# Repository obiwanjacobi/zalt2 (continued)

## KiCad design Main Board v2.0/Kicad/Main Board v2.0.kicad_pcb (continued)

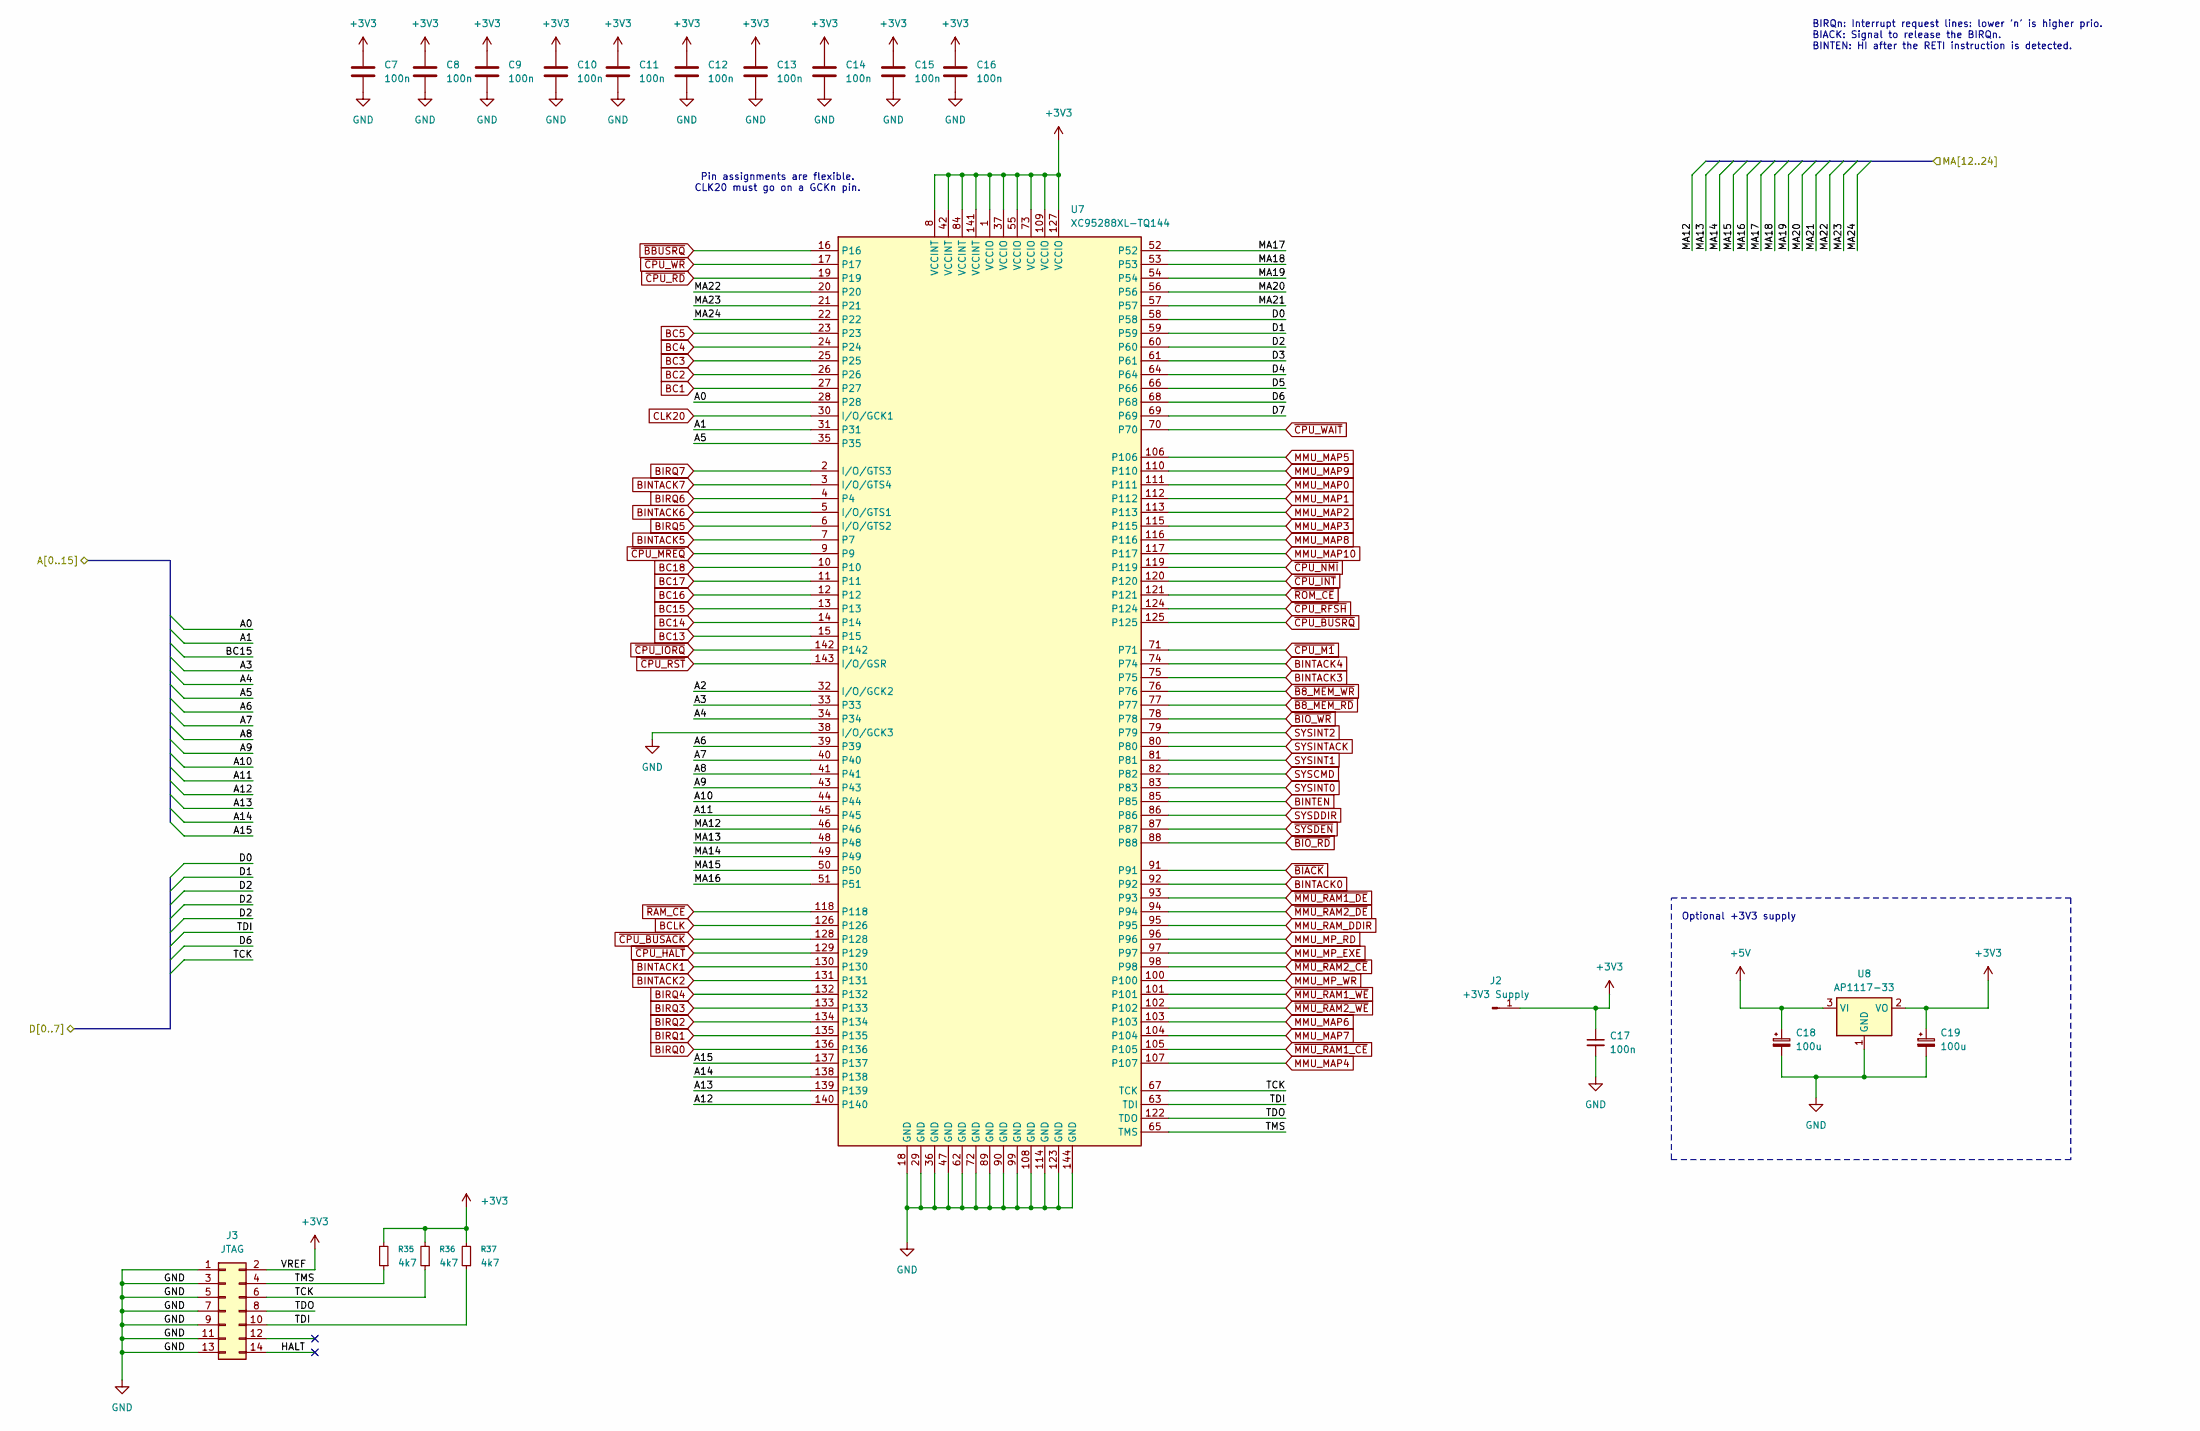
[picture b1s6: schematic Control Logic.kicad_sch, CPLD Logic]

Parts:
C7, C8, C9, C10, C11, C12, C13, C14, C15, C16, C17: 100n; C_0603_1608Metric_Pad1.08x0.95mm_HandSolder
C18, C19: 100u; CP_Radial_D8.0mm_P3.80mm
J2: +3V3 Supply; PinHeader_1x01_P2.54mm_Vertical
J3: JTAG; IDC-Header_2x07_P2.54mm_Vertical
R35, R36, R37: 4k7; R_0603_1608Metric_Pad0.98x0.95mm_HandSolder
U7: XC95288XL-TQ144; TQFP-144_20x20mm_P0.5mm
U8: AP1117-33; SOT-223-3_TabPin2

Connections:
+3V3: C7.1, C8.1, C9.1, C10.1, C11.1, C12.1, C13.1, C14.1, C15.1, C16.1, C17.1, C19.1, J2.1 (Pin_1_1), J3.2, R35.2, R36.2, R37.2, U7.1 (VCCIO), U7.8 (VCCINT), U7.37 (VCCIO), U7.42 (VCCINT), U7.55 (VCCIO), U7.73 (VCCIO), U7.84 (VCCINT), U7.109 (VCCIO), U7.127 (VCCIO), U7.141 (VCCINT), U8.2 (VO)
+5V: C18.1, U8.3 (VI); also elsewhere on the board
/CPU/A0: U7.28; also elsewhere on the board
/CPU/A1: U7.31; also elsewhere on the board
/CPU/A2: U7.32 (I/O/GCK2); also elsewhere on the board
/CPU/A3: U7.33; also elsewhere on the board
/CPU/A4: U7.34; also elsewhere on the board
/CPU/A5: U7.35; also elsewhere on the board
/CPU/A6: U7.39; also elsewhere on the board
/CPU/A7: U7.40; also elsewhere on the board
/CPU/A8: U7.41; also elsewhere on the board
/CPU/A9: U7.43; also elsewhere on the board
/CPU/A10: U7.44; also elsewhere on the board
/CPU/A11: U7.45; also elsewhere on the board
/CPU/A12: U7.140; also elsewhere on the board
/CPU/A13: U7.139; also elsewhere on the board
/CPU/A14: U7.138; also elsewhere on the board
/CPU/A15: U7.137; also elsewhere on the board
/CPU/D0: U7.58; also elsewhere on the board
/CPU/D1: U7.59; also elsewhere on the board
/CPU/D2: U7.60; also elsewhere on the board
/CPU/D3: U7.61; also elsewhere on the board
/CPU/D4: U7.64; also elsewhere on the board
/CPU/D5: U7.66; also elsewhere on the board
/CPU/D6: U7.68; also elsewhere on the board
/CPU/D7: U7.69; also elsewhere on the board
/Control Logic/HALT: J3.14
/Control Logic/MA12: U7.46; also elsewhere on the board
/Control Logic/MA13: U7.48; also elsewhere on the board
/Control Logic/MA14: U7.49; also elsewhere on the board
/Control Logic/MA15: U7.50; also elsewhere on the board
/Control Logic/MA16: U7.51; also elsewhere on the board
/Control Logic/MA17: U7.52; also elsewhere on the board
/Control Logic/MA18: U7.53; also elsewhere on the board
/Control Logic/MA19: U7.54; also elsewhere on the board
/Control Logic/MA20: U7.56; also elsewhere on the board
/Control Logic/MA21: U7.57; also elsewhere on the board
/Control Logic/MA22: U7.20; also elsewhere on the board
/Control Logic/MA23: U7.21; also elsewhere on the board
/Control Logic/MA24: U7.22; also elsewhere on the board
/Control Logic/TCK: J3.6, R36.1, U7.67 (TCK)
/Control Logic/TDI: J3.10, R37.1, U7.63 (TDI)
/Control Logic/TDO: J3.8, U7.122 (TDO)
/Control Logic/TMS: J3.4, R35.1, U7.65 (TMS)
BC1: U7.27; also elsewhere on the board
BC2: U7.26; also elsewhere on the board
BC3: U7.25; also elsewhere on the board
BC4: U7.24; also elsewhere on the board
BC5: U7.23; also elsewhere on the board
BC13: U7.15; also elsewhere on the board
BC14: U7.14; also elsewhere on the board
BC15: U7.13; also elsewhere on the board
BC16: U7.12; also elsewhere on the board
BC17: U7.11; also elsewhere on the board
BC18: U7.10; also elsewhere on the board
BCLK: U7.126; also elsewhere on the board
BINTACK0: U7.92; also elsewhere on the board
BINTACK1: U7.130; also elsewhere on the board
BINTACK2: U7.131; also elsewhere on the board
BINTACK3: U7.75; also elsewhere on the board
BINTACK4: U7.74; also elsewhere on the board
BINTACK5: U7.7; also elsewhere on the board
BINTACK6: U7.5 (I/O/GTS1); also elsewhere on the board
BINTACK7: U7.3 (I/O/GTS4); also elsewhere on the board
BINTEN: U7.85; also elsewhere on the board
BIRQ0: U7.136; also elsewhere on the board
BIRQ1: U7.135; also elsewhere on the board
BIRQ2: U7.134; also elsewhere on the board
BIRQ3: U7.133; also elsewhere on the board
BIRQ4: U7.132; also elsewhere on the board
BIRQ5: U7.6 (I/O/GTS2); also elsewhere on the board
BIRQ6: U7.4; also elsewhere on the board
BIRQ7: U7.2 (I/O/GTS3); also elsewhere on the board
CLK20: U7.30 (I/O/GCK1); also elsewhere on the board
GND: C7.2, C8.2, C9.2, C10.2, C11.2, C12.2, C13.2, C14.2, C15.2, C16.2, C17.2, C18.2, C19.2, J3.1, J3.3, J3.5, J3.7, J3.9, J3.11, J3.13, U7.18 (GND), U7.29 (GND), U7.36 (GND), U7.38 (I/O/GCK3), U7.47 (GND), U7.62 (GND), U7.72 (GND), U7.89 (GND), U7.90 (GND), U7.99 (GND), U7.108 (GND), U7.114 (GND), U7.123 (GND), U7.144 (GND), U8.1 (GND); also elsewhere on the board
MMU_MAP0: U7.111; also elsewhere on the board
MMU_MAP1: U7.112; also elsewhere on the board
MMU_MAP2: U7.113; also elsewhere on the board
MMU_MAP3: U7.115; also elsewhere on the board
MMU_MAP4: U7.107; also elsewhere on the board
MMU_MAP5: U7.106; also elsewhere on the board
MMU_MAP6: U7.103; also elsewhere on the board
MMU_MAP7: U7.104; also elsewhere on the board
MMU_MAP8: U7.116; also elsewhere on the board
MMU_MAP9: U7.110; also elsewhere on the board
MMU_MAP10: U7.117; also elsewhere on the board
MMU_MP_EXE: U7.97; also elsewhere on the board
MMU_MP_RD: U7.96; also elsewhere on the board
MMU_MP_WR: U7.100; also elsewhere on the board
MMU_RAM_DDIR: U7.95; also elsewhere on the board
SYSCMD: U7.82; also elsewhere on the board
SYSDDIR: U7.86; also elsewhere on the board
SYSINT0: U7.83; also elsewhere on the board
SYSINT1: U7.81; also elsewhere on the board
SYSINT2: U7.79; also elsewhere on the board
SYSINTACK: U7.80; also elsewhere on the board
~B8_MEM_RD: U7.77; also elsewhere on the board
~B8_MEM_WR: U7.76; also elsewhere on the board
~BBUSRQ: U7.16; also elsewhere on the board
~BIACK: U7.91; also elsewhere on the board
~BIO_RD: U7.88; also elsewhere on the board
~BIO_WR: U7.78; also elsewhere on the board
~CPU_BUSACK: U7.128; also elsewhere on the board
~CPU_BUSRQ: U7.125; also elsewhere on the board
~CPU_HALT: U7.129; also elsewhere on the board
~CPU_INT: U7.120; also elsewhere on the board
~CPU_IORQ: U7.142; also elsewhere on the board
~CPU_M1: U7.71; also elsewhere on the board
~CPU_MREQ: U7.9; also elsewhere on the board
~CPU_NMI: U7.119; also elsewhere on the board
~CPU_RD: U7.19; also elsewhere on the board
~CPU_RFSH: U7.124; also elsewhere on the board
~CPU_RST: U7.143 (I/O/GSR); also elsewhere on the board
~CPU_WAIT: U7.70; also elsewhere on the board
~CPU_WR: U7.17; also elsewhere on the board
~MMU_RAM1_CE: U7.105; also elsewhere on the board
~MMU_RAM1_DE: U7.93; also elsewhere on the board
~MMU_RAM1_WE: U7.101; also elsewhere on the board
~MMU_RAM2_CE: U7.98; also elsewhere on the board
~MMU_RAM2_DE: U7.94; also elsewhere on the board
~MMU_RAM2_WE: U7.102; also elsewhere on the board
~RAM_CE: U7.118; also elsewhere on the board
~ROM_CE: U7.121; also elsewhere on the board
~SYSDEN: U7.87; also elsewhere on the board

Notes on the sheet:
Optional +3V3 supply
Pin assignments are flexible. CLK20 must go on a GCKn pin.
BIRQn: Interrupt request lines: lower 'n' is higher prio. BIACK: Signal to release the BIRQn. BINTEN: HI after the RETI instruction is detected.

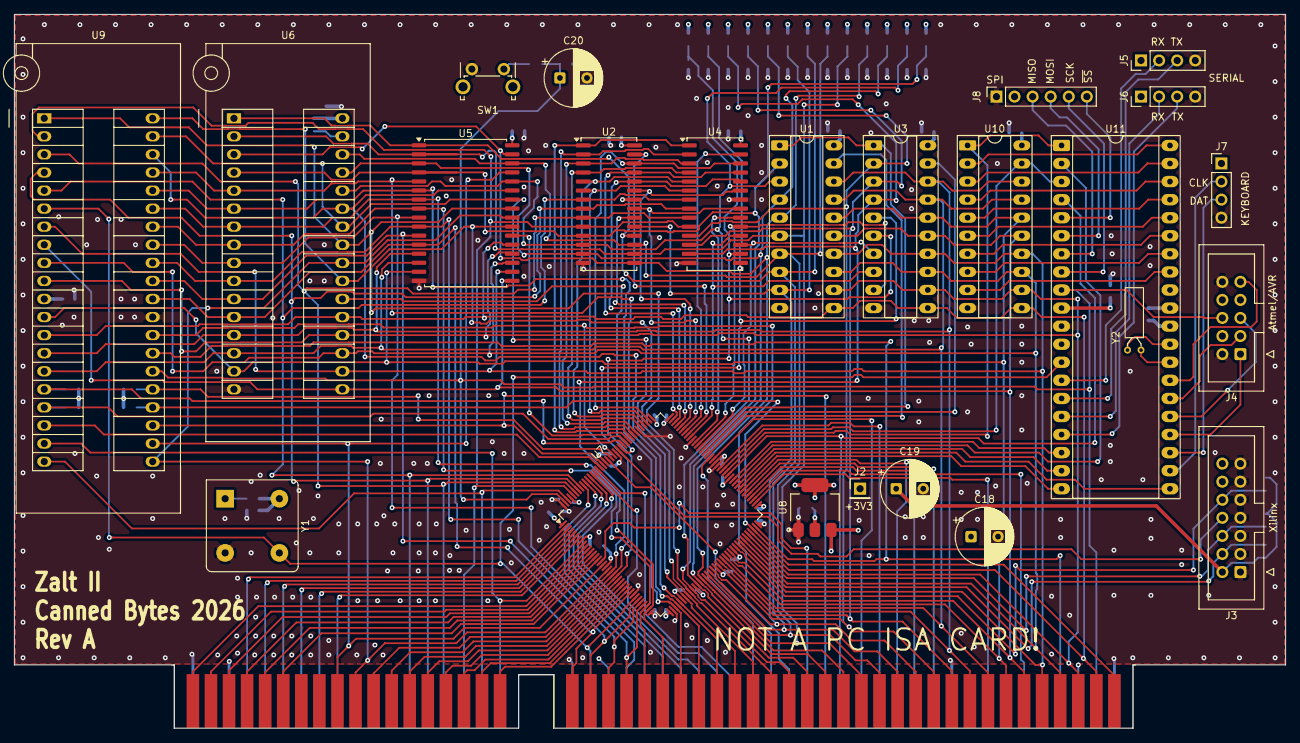
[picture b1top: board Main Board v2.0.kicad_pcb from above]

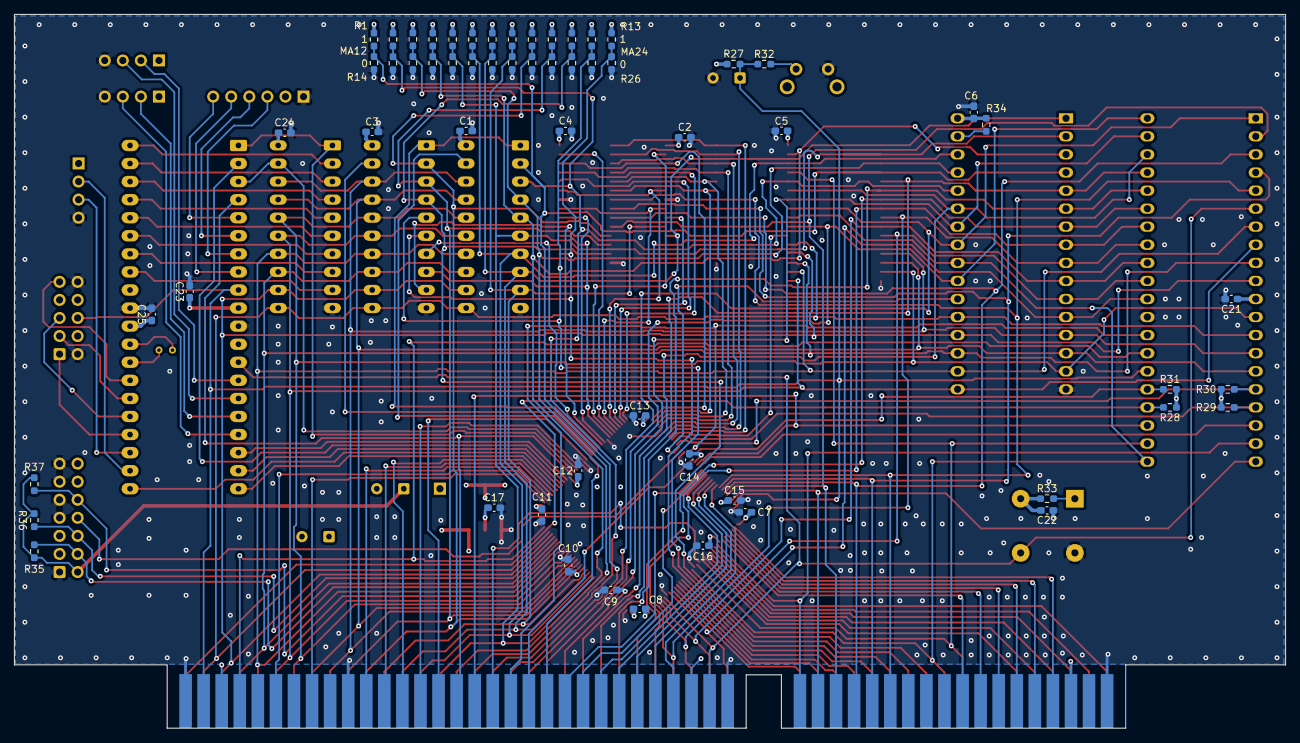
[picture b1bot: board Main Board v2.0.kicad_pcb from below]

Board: 4 copper layers, 178.7 x 100.3 mm, 84 parts (59 on the bottom side), 150 nets.

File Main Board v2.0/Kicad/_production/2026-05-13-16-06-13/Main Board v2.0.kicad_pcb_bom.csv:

Designator,Quantity,Value,Footprint,Package,MPN,DNP,Mount_Type,Description,KiLib_Generator
"C1, C10, C11, C12, C13, C14, C15, C16, C17, C2, C21, C22, C23, C24, C25, C3, C4, C5, C6, C7, C8, C9",22,100n,C_0603_1608Metric_Pad1.08x0.95mm_HandSolder,,,,smt,"[C2,C21,C22,C23,C24,C25,C3,C4,C5,C6,C7,C8,C9]Unpolarized capacitor; [C17]Unpolarized capacitor, small symbol",SMD_2terminal_chip_molded
"C18, C19, C20",3,100u,CP_Radial_D8.0mm_P3.80mm,,,,tht,"[C18,C19]Polarized capacitor, small symbol; [C20]Polarized capacitor",capacitor/THT/other
J1,1,Bus_ISA_16bit,BUS_AT,,,,tht,16-bit ISA-AT bus connector,
J2,1,+3V3 Supply,PinHeader_1x01_P2.54mm_Vertical,,,,tht,"Generic connector, single row, 01x01, script generated",connector/pin_header_socket
J3,1,JTAG,IDC-Header_2x07_P2.54mm_Vertical,,,,tht,"Generic connector, double row, 02x07, odd/even pin numbering scheme (row 1 odd numbers, row 2 even numbers), script generated (kicad-library-utils/schlib/autogen/connector/)",connector/pin_header_socket
J4,1,AVR-JTAG-10,IDC-Header_2x05_P2.54mm_Vertical,,,,tht,Atmel 10-pin JTAG connector,connector/pin_header_socket
J5,1,USART0,PinHeader_1x04_P2.54mm_Vertical,,,,tht,"Generic connector, single row, 01x04, script generated (kicad-library-utils/schlib/autogen/connector/)",connector/pin_header_socket
J6,1,USART1,PinHeader_1x04_P2.54mm_Vertical,,,,tht,"Generic connector, single row, 01x04, script generated (kicad-library-utils/schlib/autogen/connector/)",connector/pin_header_socket
J7,1,PS2KB,PinHeader_1x04_P2.54mm_Vertical,,,,tht,"Generic connector, single row, 01x04, script generated (kicad-library-utils/schlib/autogen/connector/)",connector/pin_header_socket
J8,1,SPI-SDCard,PinSocket_1x06_P2.54mm_Vertical,,,,tht,"Generic connector, single row, 01x06, script generated (kicad-library-utils/schlib/autogen/connector/)",connector/pin_header_socket
"R1, R10, R11, R12, R13, R14, R15, R16, R17, R18, R19, R2, R20, R21, R22, R23, R24, R25, R26, R27, R28, R29, R3, R30, R31, R33, R34, R4, R5, R6, R7, R8, R9",33,10k,R_0603_1608Metric_Pad0.98x0.95mm_HandSolder,,,,smt,"Resistor, small symbol",SMD_2terminal_chip_molded
R32,1,100R,R_0603_1608Metric_Pad0.98x0.95mm_HandSolder,,,,smt,"Resistor, small symbol",SMD_2terminal_chip_molded
"R35, R36, R37",3,4k7,R_0603_1608Metric_Pad0.98x0.95mm_HandSolder,,,,smt,"Resistor, small symbol",SMD_2terminal_chip_molded
SW1,1,Reset,SW_Tactile_SPST_Angled_PTS645Vx83-2LFS,,,,tht,"Push button switch, generic, two pins",
"U1, U10, U3",3,74HCT245,DIP-20_W7.62mm_Socket_LongNarrowPads,,,,tht,"Octal BUS Transceivers, 3-State outputs",package/DIP/legacy
U11,1,ATmega1284-P,DIP-40_W15.24mm_Socket_LongPads,,,,tht,"20MHz, 128kB Flash, 16kB SRAM, 4kB EEPROM, JTAG, DIP-40",package/DIP/legacy
"U2, U4",2,GLT725608,SOJ-28_7.62x18.415mm_P1.27mm,,,,smt,"32Kx8 bit Low Power CMOS Static RAM, 25/45ns, Automotive",package/gullwing
U5,1,AS6C4008-55PCN,SOP-32_11.305x20.495mm_P1.27mm,,,,smt,"512K x 8 Low Power CMOS RAM, DIP-32",package/gullwing
U6,1,AM29F040B,3M_Textool_232-1288-00-0602J_2x16_P2.54mm,,,,tht,"512K x 8 Low Power CMOS Flash, DIP-32",
U7,1,XC95288XL-TQ144,TQFP-144_20x20mm_P0.5mm,,,,smt,"CPLD, 288 Macrocells, 6400 Usable Gates",package/gullwing
U8,1,AP1117-33,SOT-223-3_TabPin2,,,,smt,"1A Low Dropout regulator, positive, 3.3V fixed output, SOT-223",
U9,1,Z80CPU,3M_Textool_240-1288-00-0602J_2x20_P2.54mm,,,,tht,"8-bit General Purpose Microprocessor, DIP-40",
Y1,1,20MHz,Oscillator_DIP-8_LargePads,,,,tht,"Crystal Clock Oscillator, DIP14-style metal package",
Y2,1,32.768kHz,Crystal_C26-LF_D2.1mm_L6.5mm_Horizontal,,,,tht,Two pin crystal,crystal_resonator_oscillator

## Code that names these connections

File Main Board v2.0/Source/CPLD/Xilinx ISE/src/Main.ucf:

# User Constraints File (UCF)
# Device: XC95288XL-TQ144
# Board:  Zalt2 Main Board v2.0 (U7)
# Generated from: Main Board v2.0 schematic / IPC netlist (2026-05-13)
#
# Naming conventions:
#   Active-low signals use the _N suffix.
#   Hierarchical net names from the schematic (e.g. /CPU/A0, Control Logic/MA22)
#   are flattened to their signal portion only.
#
# Note: JTAG dedicated pins (TDI=P63, TMS=P65, TCK=P67, TDO=P122) are fixed
#       in silicon and require no LOC constraints.
#
# Power/GND pins (no constraints needed):
#   VCC (+3V3): P1  P8  P37 P42 P55 P73 P84 P109 P127 P141
#   GND:        P18 P29 P36 P47 P62 P72 P89  P90  P99 P108 P114 P123 P144

# ----------------------------------------------------------------------------
# Clocks
# ----------------------------------------------------------------------------

NET "CLK20" LOC = "P30" | BUFG = "CLK" ;
NET "BCLK" LOC = "P126" | SLEW = "FAST" | DRIVE = "8" ;

NET "CLK20" TNM_NET = "CLK20" | CLOCK_DEDICATED_ROUTE = TRUE;
TIMESPEC "TS_CLK20" = PERIOD "CLK20" 50 ns HIGH 50 % ;

#NET "BCLK"    TNM_NET = "BCLK" ;
#TIMESPEC "TS_BCLK" = PERIOD "BCLK" 100 ns HIGH 50 % ;

# ----------------------------------------------------------------------------
# CPU Bus - Address (inputs from Z80)
# ----------------------------------------------------------------------------

NET "A<0>" LOC = "P28" ;
NET "A<1>" LOC = "P31" ;
NET "A<2>" LOC = "P32" ;
NET "A<3>" LOC = "P33" ;
NET "A<4>" LOC = "P34" ;
NET "A<5>" LOC = "P35" ;
NET "A<6>" LOC = "P39" ;
NET "A<7>" LOC = "P40" ;
NET "A<8>" LOC = "P41" ;
NET "A<9>" LOC = "P43" ;
NET "A<10>" LOC = "P44" ;
NET "A<11>" LOC = "P45" ;
NET "A<12>" LOC = "P140" ;
NET "A<13>" LOC = "P139" ;
NET "A<14>" LOC = "P138" ;
NET "A<15>" LOC = "P137" ;

# ----------------------------------------------------------------------------
# CPU Bus - Data (bidirectional with Z80)
# ----------------------------------------------------------------------------

NET "D<0>" LOC = "P58"  ;
NET "D<1>" LOC = "P59"  ;
NET "D<2>" LOC = "P60"  ;
NET "D<3>" LOC = "P61"  ;
NET "D<4>" LOC = "P64"  ;
NET "D<5>" LOC = "P66"  ;
NET "D<6>" LOC = "P68"  ;
NET "D<7>" LOC = "P69"  ;

# ----------------------------------------------------------------------------
# CPU Control Signals (active-low signals use _N suffix)
# ----------------------------------------------------------------------------

NET "CPU_MREQ_N" LOC = "P9" ;
NET "CPU_IORQ_N" LOC = "P142" ;
NET "CPU_RD_N" LOC = "P19" ;
NET "CPU_WR_N" LOC = "P17" ;
NET "CPU_M1_N" LOC = "P71" ;
NET "CPU_RFSH_N" LOC = "P124" ;
NET "CPU_HALT_N" LOC = "P129" ;
NET "CPU_WAIT_N" LOC = "P70" ;
NET "CPU_INT_N" LOC = "P120" ;
NET "CPU_NMI_N" LOC = "P119" ;
NET "CPU_RST_N" LOC = "P143" | BUFG = "SR" ;
NET "CPU_BUSRQ_N" LOC = "P125" ;
NET "CPU_BUSACK_N" LOC = "P128" ;

# ----------------------------------------------------------------------------
# Memory Chip Selects (outputs from CPLD)
# ----------------------------------------------------------------------------

NET "ROM_CE_N" LOC = "P121" ;
NET "RAM_CE_N" LOC = "P118" ;

# ----------------------------------------------------------------------------
# MMU - Physical Memory Address Extension (inputs from MMU address lines)
# ----------------------------------------------------------------------------

NET "MA<12>" LOC = "P46" ;
NET "MA<13>" LOC = "P48" ;
NET "MA<14>" LOC = "P49" ;
NET "MA<15>" LOC = "P50" ;
NET "MA<16>" LOC = "P51" ;
NET "MA<17>" LOC = "P52" ;
NET "MA<18>" LOC = "P53" ;
NET "MA<19>" LOC = "P54" ;
NET "MA<20>" LOC = "P56" ;
NET "MA<21>" LOC = "P57" ;
NET "MA<22>" LOC = "P20" ;
NET "MA<23>" LOC = "P21" ;
NET "MA<24>" LOC = "P22" ;

# ----------------------------------------------------------------------------
# MMU - Mapping RAM Control
# ----------------------------------------------------------------------------

NET "MMU_MAP<0>" LOC = "P111" ;
NET "MMU_MAP<1>" LOC = "P112" ;
NET "MMU_MAP<2>" LOC = "P113" ;
NET "MMU_MAP<3>" LOC = "P115" ;
NET "MMU_MAP<4>" LOC = "P107" ;
NET "MMU_MAP<5>" LOC = "P106" ;
NET "MMU_MAP<6>" LOC = "P103" ;
NET "MMU_MAP<7>" LOC = "P104" ;
NET "MMU_MAP<8>" LOC = "P116" ;
NET "MMU_MAP<9>" LOC = "P110" ;
NET "MMU_MAP<10>" LOC = "P117" ;

NET "MMU_RAM1_CE_N" LOC = "P105" ;
NET "MMU_RAM2_CE_N" LOC = "P98" ;
NET "MMU_RAM1_WE_N" LOC = "P101" ;
NET "MMU_RAM2_WE_N" LOC = "P102" ;
NET "MMU_RAM1_DE_N" LOC = "P93" ;
NET "MMU_RAM2_DE_N" LOC = "P94" ;
NET "MMU_RAM_DDIR" LOC = "P95" ;

# ----------------------------------------------------------------------------
# MMU - Memory Protection Unit signals
# ----------------------------------------------------------------------------

NET "MMU_MP_EXE" LOC = "P97"  ;
NET "MMU_MP_RD" LOC = "P96"  ;
NET "MMU_MP_WR" LOC = "P100"  ;

# ----------------------------------------------------------------------------
# Expansion Bus - IRQ / INTACK daisy-chain
# ----------------------------------------------------------------------------

NET "BIRQ<0>" LOC = "P136"  ;
NET "BIRQ<1>" LOC = "P135"  ;
NET "BIRQ<2>" LOC = "P134"  ;
NET "BIRQ<3>" LOC = "P133"  ;
NET "BIRQ<4>" LOC = "P132"  ;
NET "BIRQ<5>" LOC = "P6"   ;
NET "BIRQ<6>" LOC = "P4"   ;
NET "BIRQ<7>" LOC = "P2"   ;

NET "BINTACK<0>" LOC = "P92" ;
NET "BINTACK<1>" LOC = "P130" ;
NET "BINTACK<2>" LOC = "P131" ;
NET "BINTACK<3>" LOC = "P75" ;
NET "BINTACK<4>" LOC = "P74" ;
NET "BINTACK<5>" LOC = "P7"  ;
NET "BINTACK<6>" LOC = "P5"  ;
NET "BINTACK<7>" LOC = "P3"  ;

NET "BINTEN" LOC = "P85" ;
NET "BIACK_N" LOC = "P91" ;
NET "BBUSRQ_N" LOC = "P16" ;

# ----------------------------------------------------------------------------
# Expansion Bus - Memory / IO Strobes (outputs to expansion bus)
# ----------------------------------------------------------------------------

NET "B8_MEM_WR_N" LOC = "P76" ;
NET "B8_MEM_RD_N" LOC = "P77" ;
NET "BIO_WR_N" LOC = "P78" ;
NET "BIO_RD_N" LOC = "P88" ;

# ----------------------------------------------------------------------------
# Expansion Bus - Bus Control Lines
# ----------------------------------------------------------------------------

NET "BC1" LOC = "P27"  ;
NET "BC2" LOC = "P26"  ;
NET "BC3" LOC = "P25"  ;
NET "BC4" LOC = "P24"  ;
NET "BC5" LOC = "P23"  ;
NET "BC13" LOC = "P15"  ;
NET "BC14" LOC = "P14"  ;
NET "BC15" LOC = "P13"  ;
NET "BC16" LOC = "P12"  ;
NET "BC17" LOC = "P11"  ;
NET "BC18" LOC = "P10"  ;

# IO/GCK3 to GND (big mistake!)
NET "GNDPIN" LOC = "P38" ;

# ----------------------------------------------------------------------------
# System Interface (MCU <-> CPLD)
# ----------------------------------------------------------------------------

NET "SYSINT<0>" LOC = "P83"  ;
NET "SYSINT<1>" LOC = "P81"  ;
NET "SYSINT<2>" LOC = "P79"  ;
NET "SYSINTACK" LOC = "P80" ;
NET "SYSCMD" LOC = "P82" ;
NET "SYSDDIR" LOC = "P86" ;
NET "SYSDEN_N" LOC = "P87" ;

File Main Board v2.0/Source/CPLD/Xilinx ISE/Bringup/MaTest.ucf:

# User Constraints File (UCF)
# Device: XC95288XL-TQ144
# Board:  Zalt2 Main Board v2.0 (U7) - all other chips removed for this test
#
# Pin locations match Main.ucf so the same physical net (MA<12..24> + its
# R1-R26 pull-ups) is being tested, without touching the real Main design.

NET "MA<12>" LOC = "P46" ;
NET "MA<13>" LOC = "P48" ;
NET "MA<14>" LOC = "P49" ;
NET "MA<15>" LOC = "P50" ;
NET "MA<16>" LOC = "P51" ;
NET "MA<17>" LOC = "P52" ;
NET "MA<18>" LOC = "P53" ;
NET "MA<19>" LOC = "P54" ;
NET "MA<20>" LOC = "P56" ;
NET "MA<21>" LOC = "P57" ;
NET "MA<22>" LOC = "P20" ;
NET "MA<23>" LOC = "P21" ;
NET "MA<24>" LOC = "P22" ;

# Expansion bus header pin, unused with no card plugged in - safe probe point
NET "MA_ALL_HIGH" LOC = "P27" ;   # BC1 in Main.ucf

# Per-bit passthrough for a logic analyzer - spare pins, all chips removed
#NET "MA_BITS<12>" LOC = "P26" ;   # BC2
#NET "MA_BITS<13>" LOC = "P25" ;   # BC3
#NET "MA_BITS<14>" LOC = "P24" ;   # BC4
#NET "MA_BITS<15>" LOC = "P23" ;   # BC5
#NET "MA_BITS<16>" LOC = "P15" ;   # BC13
#NET "MA_BITS<17>" LOC = "P14" ;   # BC14
#NET "MA_BITS<18>" LOC = "P13" ;   # BC15
#NET "MA_BITS<19>" LOC = "P12" ;   # BC16
#NET "MA_BITS<20>" LOC = "P11" ;   # BC17
#NET "MA_BITS<21>" LOC = "P10" ;   # BC18
#NET "MA_BITS<22>" LOC = "P111" ;  # MMU_MAP0
#NET "MA_BITS<23>" LOC = "P112" ;  # MMU_MAP1
#NET "MA_BITS<24>" LOC = "P113" ;  # MMU_MAP2

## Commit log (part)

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2026-03-28 initial
2026-03-30 cleanup
2026-04-06 schematic done*
2026-04-08 board update
2026-04-11 schematic update
2026-04-11 structure
2026-04-11 docs
2026-04-13 schematic updates
2026-04-13 add mcu proj
2026-04-15 dcos
2026-04-15 board
2026-04-20 new chats
2026-04-22 code sections
2026-04-24 os doc
2026-05-02 board progress
2026-05-11 board rev a routed
2026-05-13 final board
2026-05-14 cpld - add vhdl sources
2026-05-15 MCU code setup
2026-05-15 reorganize
2026-05-16 display docs
2026-05-16 fix workspace
2026-05-16 fix atl lib
2026-05-16 rtc and console protocol
2026-05-16 locking on public data api
2026-05-16 chat smart device for storage
2026-05-16 lcd wiki link
2026-05-16 update schematic
2026-05-16 more docs
2026-05-17 connect data protocol to main loop
2026-05-17 compiler/build segmentation + loader
2026-05-18 chats and docs
2026-05-20 chat + docs
2026-05-20 mmu routines
2026-05-20 page zero
2026-05-20 fix build
2026-05-21 jlcpcb prod issue
2026-05-23 zero page plumbing
2026-05-24 tdo/tdi swap text
2026-05-24 prod issue conclusion
2026-05-24 cpld not jtagging
2026-05-24 os task switch
2026-05-25 rst with switch to os-task
2026-05-25 dummy os api stubs
2026-05-25 app build
2026-05-26 c section
2026-05-30 mem. ring and defc - build
2026-05-31 lib api
2026-05-31 doxygen
2026-05-31 update jtag schematic comments
2026-06-01 null impl for cpld
2026-06-01 z80 ice docs
